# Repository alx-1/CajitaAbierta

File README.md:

# CajitaAbierta

The repo for the firmware is now at : https://gitlab.com/darknessdesigner/cajitaabierta

Start with the howtos : https://github.com/alx-1/CajitaAbierta/wiki

Breakout wireless sensor circuit + software for the nodemcu ESP32S board.

Can send sensor data to :

touchOSCBridge

chataigne

hydra over node

and the TDLF module : https://github.com/alx-1/technologies-de-la-fete

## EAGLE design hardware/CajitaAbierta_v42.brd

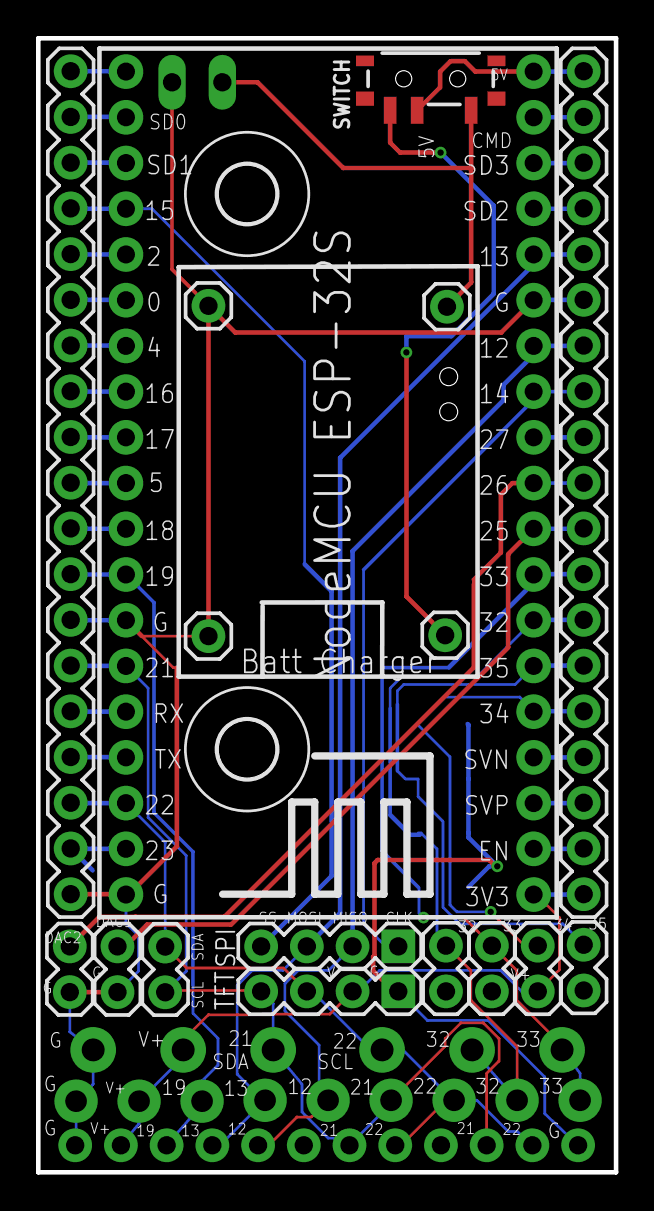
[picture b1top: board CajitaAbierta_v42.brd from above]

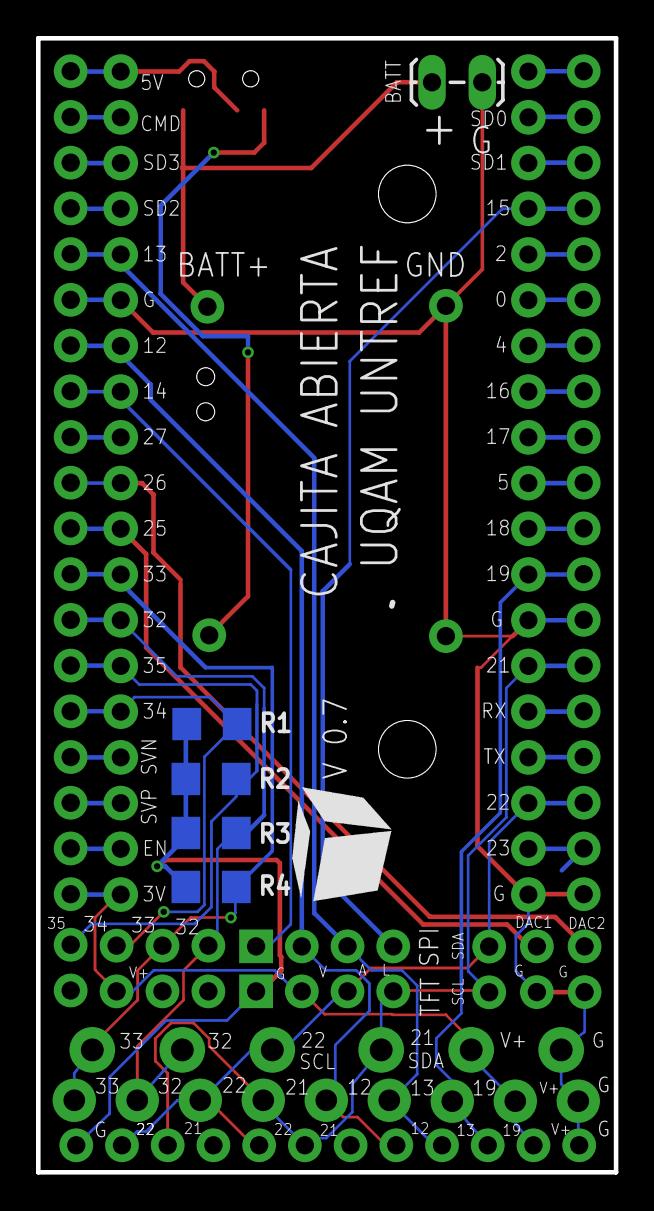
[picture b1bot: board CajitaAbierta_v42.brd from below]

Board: 2 copper layers, 32.1 x 63.0 mm, 30 parts (5 on the bottom side), 38 nets.

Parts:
5V_IN: 5V_IN; 1X01
32, 33, 34, 35: 1X02
BAT-: 1X01
BATT: 1X02_LOCK_LONGPADS
BATT+: 1X01
DAC1, DAC2: 1X02
GND: Batt Charger; 1X01
I2C: 1X02
J1: 1X12_NO_SILK
JP9, JP10: 1X19
R1, R2, R3, R4: 1206
SPI: 1X04
SWITCH: SWITCH_SPST_SMD_A
T1, T2, T3: SCREWTERMINAL-3.5MM-3-NS
TFT: 1X04
U$1, U$2: 3,2
U$3: ESP32DEVKITC; ESP32-DEVKITC
U$4, U$5: SCREW_TERMINAL_3_POS_5MM

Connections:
3V3: 34.1, J1.2, JP9.1, T1.2, TFT.2, U$3.1, U$4.2
5V: JP9.19, SWITCH.2, U$3.19
5V_IN: 5V_IN.1, SWITCH.1
ADC4: 32.2, JP9.7, R3.2, T3.2, U$3.7, U$5.2
ADC5: 33.2, JP9.8, R4.2, T3.3, U$3.8, U$5.3
ADC6: 34.2, JP9.5, R1.2, U$3.5
ADC7: 35.2, JP9.6, R2.2, U$3.6
BATT+: BATT.2, BATT+.1, SWITCH.3
CLK: JP10.19, U$3.20
CMD: JP9.18, U$3.18
D1: JP10.2, U$3.37
D2: J1.3, JP10.8, T1.3, U$3.31
D3: JP10.9, U$3.30
D4: JP10.10, U$3.29
D5: JP10.13, U$3.26
D6: JP10.14, U$3.25
D7: JP9.11, U$3.11
D8: JP10.15, U$3.24
DAC1: DAC1.1, JP9.9, U$3.9
DAC2: DAC2.1, JP9.10, U$3.10
EN: JP9.2, U$3.2
GND: BAT-.1, BATT.1, DAC1.2, DAC2.2, GND.1, J1.1, J1.12, JP9.14, JP10.1, JP10.7, R1.1, R2.1, R3.1, R4.1, T1.1, TFT.1, U$3.14, U$3.32, U$3.38, U$4.1
I2C_SCL: I2C.2, J1.8, J1.11, JP10.3, T3.1, TFT.3, U$3.36, U$5.1
I2C_SDA: I2C.1, J1.7, J1.10, JP10.6, T2.3, TFT.4, U$3.33, U$4.3
IO16: JP10.12, U$3.27
IO17: JP10.11, U$3.28
MISO: J1.5, JP9.13, SPI.2, T2.2, U$3.13
MOSI: J1.4, JP9.15, SPI.3, T2.1, U$3.15
RXD0: JP10.5, U$3.34
SD0: JP10.18, U$3.21
SD1: JP10.17, U$3.22
SD2: JP9.16, U$3.16
SD3: JP9.17, U$3.17
SPI_CLK: JP9.12, SPI.1, U$3.12
SPI_SS: JP10.16, SPI.4, U$3.23
SVN: JP9.4, U$3.4
SVP: JP9.3, U$3.3
TXD0: JP10.4, U$3.35

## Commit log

2021-10-01 Initial commit
    Cajita Abierta para enseñar. 'Breakout' board para el Nodemcu ESP32-S. Con 8 salidas/entradas io (servos, luces), 4 analog in para sensores, 2 DACs, SPI, I2C, mini pantallas.
2021-10-01 imagen de la plaqueta
2021-10-01 Added labels
2021-10-01 Last minute changes to version 0.3
2021-10-07 Voltage divider uses V+ as variable resistance
    For Yesi :)
2021-10-16 Arduino Websocket connection to a server
2021-10-23 UDP_OSC
2021-11-07 Updates for ESP32
    Adapted the previous example to work with an ESP32. Udp.write becomes Udp.print and a delay(50) was added to try to get the terminal window to print messages correctly. Unsure why it doesn't work.
2021-11-08 v04 - changes to the TFT connections
    nouvelles étiquettes (labels)
    cambié sdl and sda
    switch on the other side
2021-11-10 Adding support for the TFT screen
2021-11-17 images_code_ino
2021-12-05 V0.4
    Works with tdlf -> UDP send of sensor data.
2022-05-13 added the reception of a message from the server to the client
    A condition and ESP.restart()
2022-06-09 Now with screw terminals
    More code examples
2022-07-07 Dos nuevas versiones!
    v0.5 : Avec borniers pour les cours de robotique
    v0.42 : 'Sitck' pour interfacer avec des capteurs : Accéléromètre, Pression et autres senseurs analogiques.
2022-07-07 Create CajitaAbierta_stick v8.step
    3D case for the stick sensor
2022-07-07 Create tdlf_cajita_abierta_stick_v0.42.ino
    Code for the 'stick' version of the Cajita Abierta. Features :
    MDNS discovery
    Web configuration
    Interface with Accelerometer, Pressure sensors as well as 4 analogical sensors inputs.
    OSC midi support.
2022-07-09 Update tdlf_cajita_abierta_stick_v0.42.ino
    Switched to LITTLEFS
    Improvements on modes and usability
2022-08-16 A little docs and modifs
2022-11-27 Moving to a single board with
    5mm screw terminals for heavier motor controls
    3.5mm screw terminals for lighter wear
    Accelerometer pinout, breath sensor pinout
2023-02-23 Refactoring the code
    Splitting of the main sensors and functions into separate files
    Captive web portal for the configuration and operation
2023-03-05 Almost done with the recording / playback
2023-03-09 Gimnasio de arte
2023-03-21 Cajita Abierta v.0.46
    OTA uploading of .bin file
2023-03-23 mdns server selection works
2023-03-27 v0.47 getting ready for min max ranging through the web portal
    // (done) * improve .bin upload interface
    // (done) * fix bug Sensor1 preferences saving
    // (done) * actually select udp destination (tdlf, chataigne, touchoscbridge) sending based on the user's choice
    // (done) * switch to asynchronous mode to enable ranging via the captive portal
2023-03-31 EMA filter implemented
    You need to go to http://192.168.1.1/calibrate to test it out.
2023-04-18 Better sensor config
2023-04-18 Images for the web updater
2023-04-18 binary file
2023-05-02 New dir and example use for Chataigne
2023-05-02 images for chataigne config
2023-05-06 cajita abierta -> chataigne -> ossia
    Some media for documenting how to get data from the cajita into ossia via chataigne
2023-05-06 media for ossia howto
2023-05-06 move them files
2023-05-07 Files for the hydra example
2023-05-07 An image
2023-05-07 Cropped image for the wiki
2023-05-07 Unique names for multiple cajitas
2023-05-10 Petit changement au README
2023-05-16 Recording data and setting the array size
2023-09-04 moving the firmware to https://gitlab.com/darknessdesigner/cajitaabierta

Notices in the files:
parts and their libraries:
SparkFun-Connectors: Licensing: Creative Commons ShareAlike 4.0 International - https://creativecommons.org/licenses/by-sa/4.0
